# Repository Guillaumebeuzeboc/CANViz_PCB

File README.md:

# CANViz_PCB
CANViz shield PCB for stm32f428i-DISC1 with Kicad

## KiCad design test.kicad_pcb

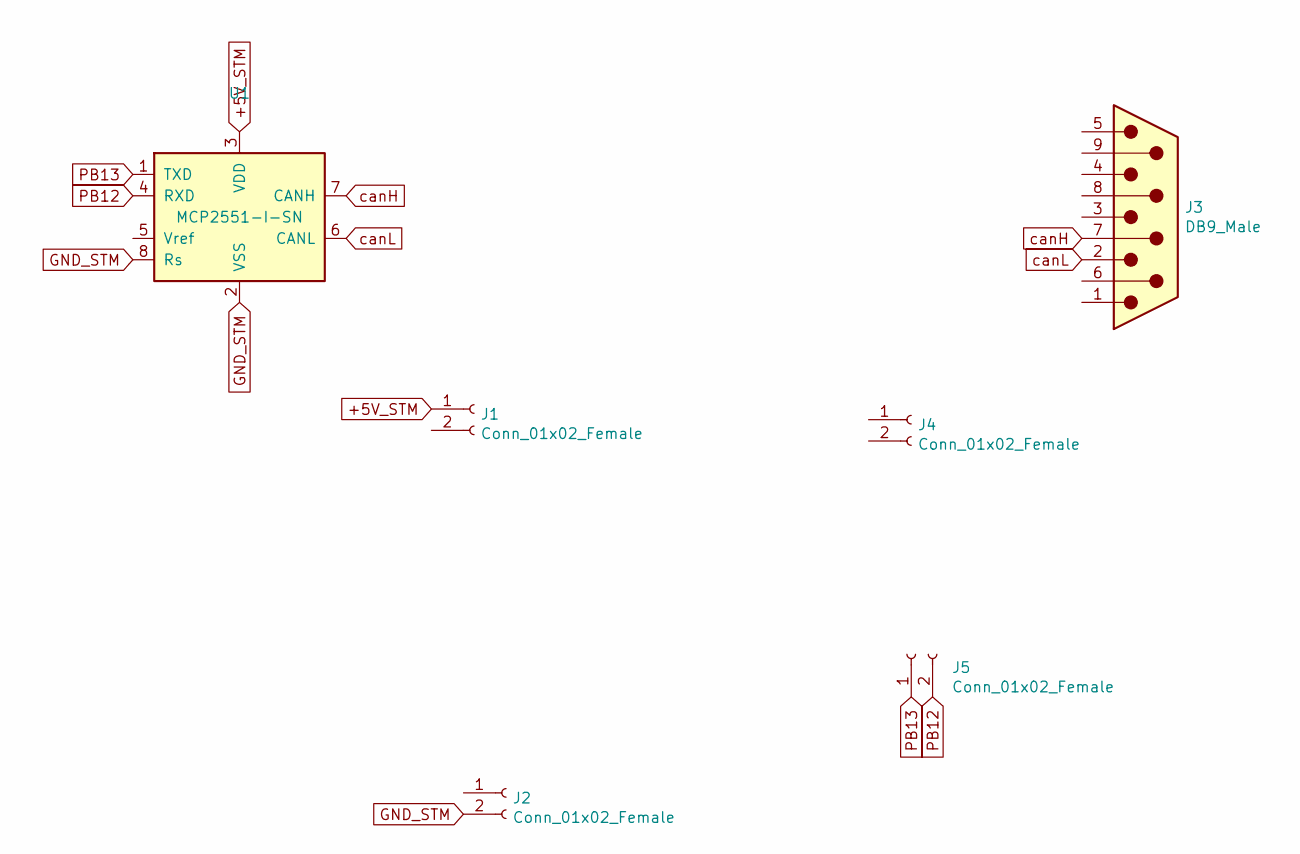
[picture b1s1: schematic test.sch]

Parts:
J1, J2, J4, J5: Conn_01x02_Female; PinSocket_1x02_P2.54mm_Vertical
J3: DB9_Male; DSUB-9_Male_Horizontal_P2.77x2.84mm_EdgePinOffset4.94mm_Hou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
U1: MCP2551-I-SN; SOIC-8_3.9x4.9mm_P1.27mm

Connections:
+5V_STM: J1.1, U1.3 (VDD)
GND_STM: J2.2, U1.2 (VSS), U1.8 (Rs)
PB12: J5.2, U1.4 (RXD)
PB13: J5.1, U1.1 (TXD)
canH: J3.7, U1.7 (CANH)
canL: J3.2, U1.6 (CANL)

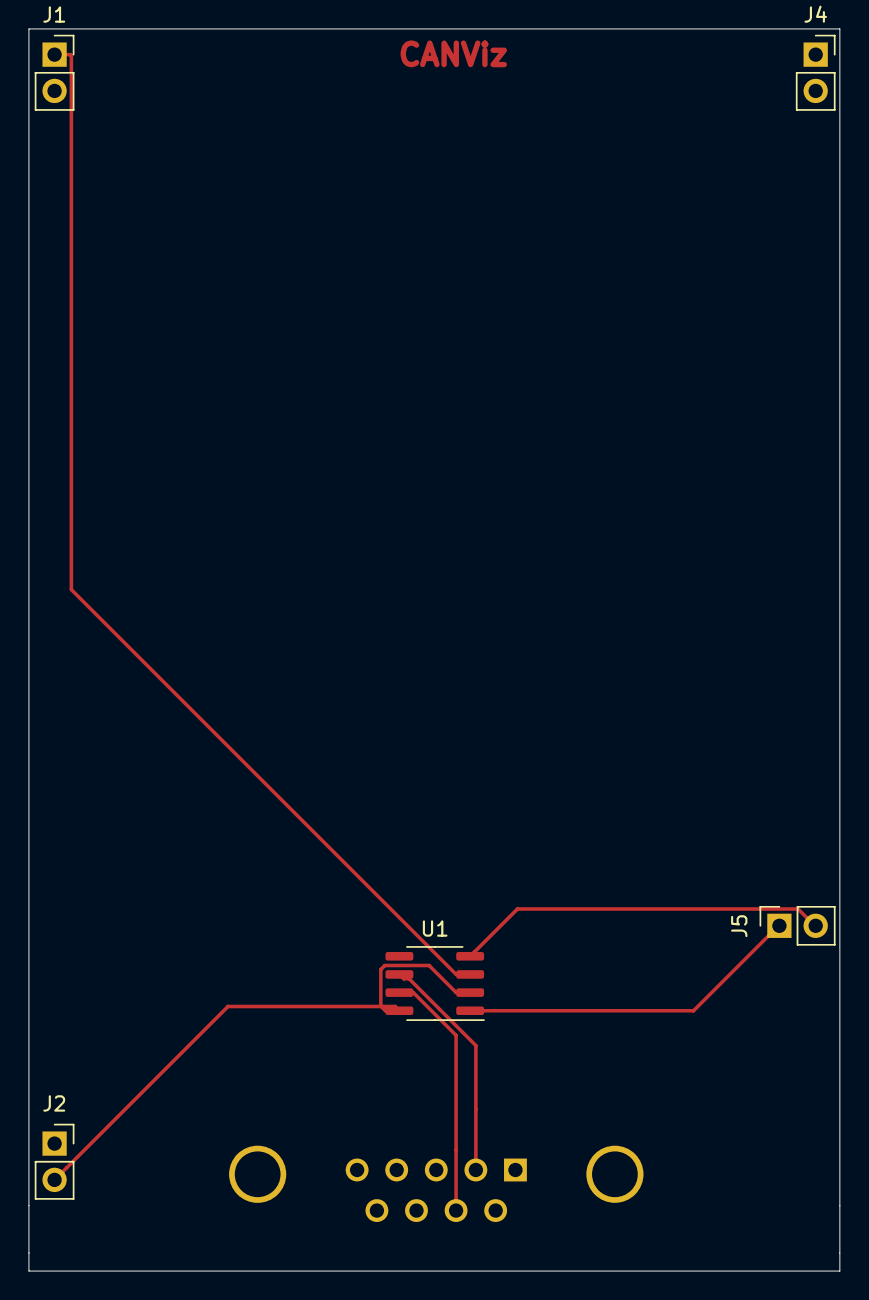
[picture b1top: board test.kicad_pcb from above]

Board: 2 copper layers, 56.7 x 86.9 mm, 6 parts (1 on the bottom side), 6 nets.

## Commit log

2020-02-05 First version with correct dimensions
2020-02-12 Update db9 position for CAD
2020-02-13 use less pin sockets
2020-02-13 generate .step file of new PCB
2020-02-18 Gerbers and BOM files
2020-02-18 don't track zip files
2020-02-19 housed db9
2020-02-19 change shape of PCB due to new db9
2020-02-21 update gerbers
2020-02-21 regular mcp2551
